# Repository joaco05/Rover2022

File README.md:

# Rover2022
Rover para clases iniciales. Cerrado y compacto para evitar desconexiones y problemas electricos. Basado en placa Controladora PCB BC2019 (Arduino Nano, driver motores, sensor ultrasonico, sensores IR, conectores) Alimentacion 2 x 3,7V (alimentacion del driver de motores, independiente de Arduino)<br><br>
<b>Printer 3D</b>
Se imprime sin soportes, altura 0,20 o 0,25. Solo las ruedas quedan mejor en modo VASE

<br><br>
<b>ARMADO</b>
El pack de baterias debe ubicarse lo mas adelante posible. Los soportes de motor deberan ir justo despues del borde curvo del chassis, de manera tal que el eje del motor quede al menos 10mm detras del borde.
Esto apunta a que el centro de gravedad se desplace mas cerca de los ejes permitiendo una mejor traccion y evitando patinada de ruedas.

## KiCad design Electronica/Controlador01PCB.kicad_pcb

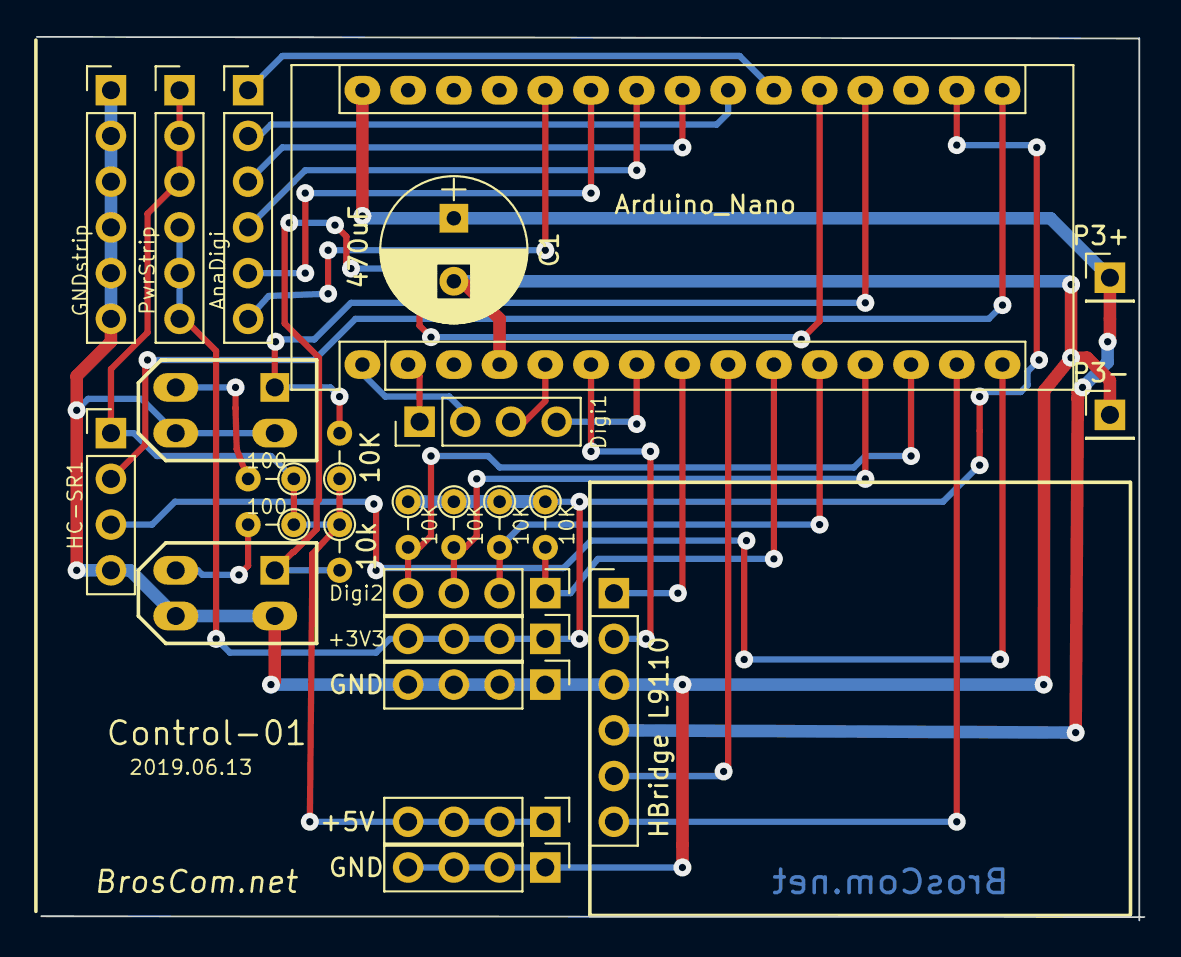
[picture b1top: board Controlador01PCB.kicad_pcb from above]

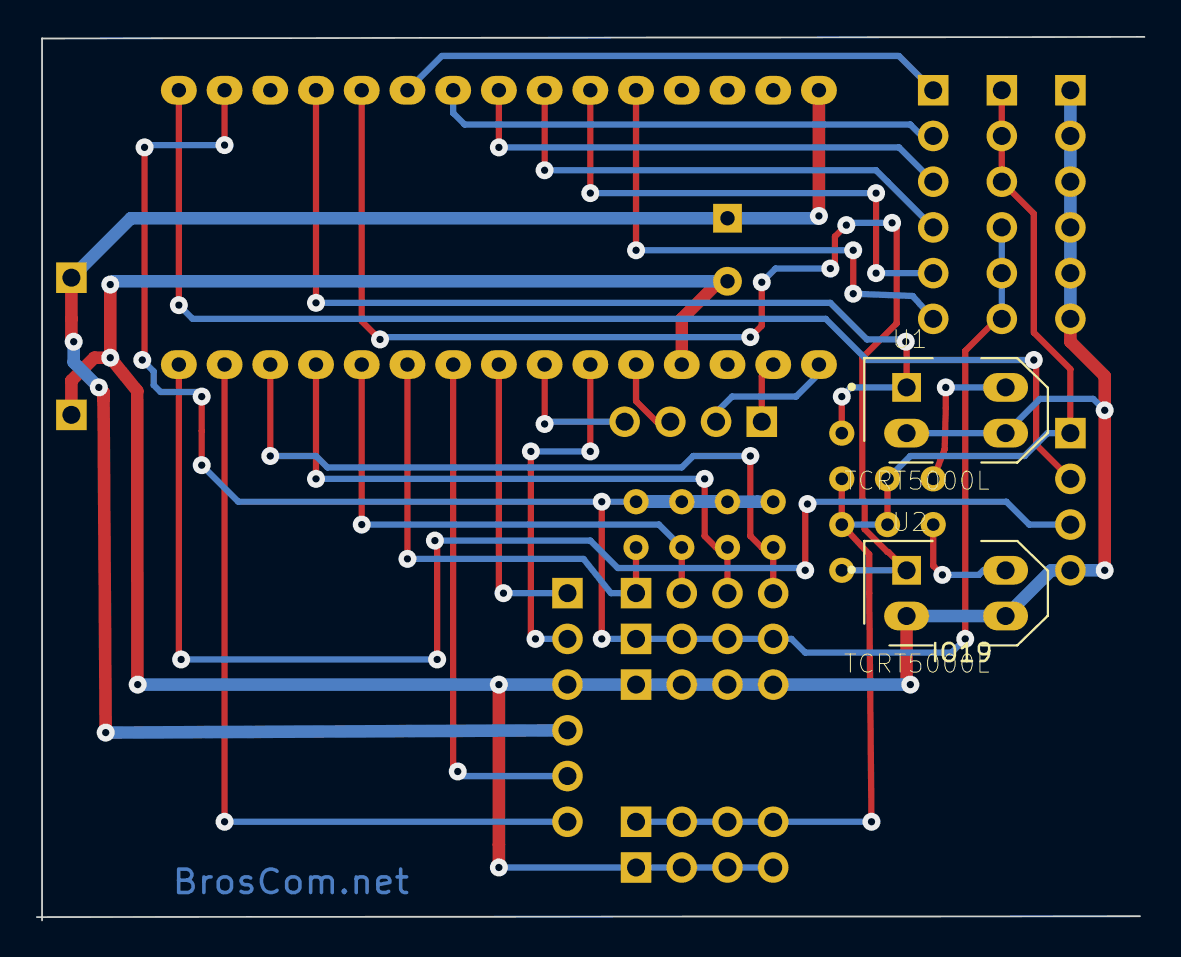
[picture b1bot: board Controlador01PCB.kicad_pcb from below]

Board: 2 copper layers, 61.5 x 49.1 mm, 25 parts (2 on the bottom side), 28 nets.

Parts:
A1: Arduino_Nano
C1: 470uF; CP_Radial_D8.0mm_P3.50mm
GNDstrip1: GNDstrip; Pin_Header_Straight_1x06_Pitch2.54mm
HC-SR1: Ultrasonic; Pin_Header_Straight_1x04_Pitch2.54mm
P1: HBridge L9110; Pin_Header_Straight_1x06_Pitch2.54mm
P2: AnaDigi; Pin_Header_Straight_1x06_Pitch2.54mm
P3: Digi1; Pin_Header_Straight_1x04_Pitch2.54mm
P3+, P3-: CONN_01X01; Pin_Header_Straight_1x01_Pitch2.54mm
P3G1, P4G1: GND; Pin_Header_Straight_1x04_Pitch2.54mm
P3V1: +5V; Pin_Header_Straight_1x04_Pitch2.54mm
P4: Digi2; Pin_Header_Straight_1x04_Pitch2.54mm
P4V1: +3V3; Pin_Header_Straight_1x04_Pitch2.54mm
PwrStrip1: PwrStrip; Pin_Header_Straight_1x06_Pitch2.54mm
R1, R5, R6, R7, R8: 10K; R_Axial_DIN0204_L3.6mm_D1.6mm_P2.54mm_Vertical
R2: 10k; R_Axial_DIN0204_L3.6mm_D1.6mm_P2.54mm_Vertical
R3, R4: 100; R_Axial_DIN0204_L3.6mm_D1.6mm_P2.54mm_Vertical
U1, U2: TCRT5000L; XDCR_TCRT5000L

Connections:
+3V3: A1.17, P4V1.1, P4V1.2, P4V1.3, P4V1.4, PwrStrip1.4, PwrStrip1.5, PwrStrip1.6, R5.1, R6.1, R7.1, R8.1
+5V: HC-SR1.1, P3V1.1, P3V1.2, P3V1.3, P3V1.4, PwrStrip1.1, PwrStrip1.2, PwrStrip1.3, R1.1, R2.1, R3.1, R4.1
D7: A1.10, P4.1, R5.2
D8: A1.11, P4.2, R6.2
D9: A1.12, P4.3, R7.2
D10: A1.13, P4.4, R8.2
GND: A1.4, C1.2, GNDstrip1.1, GNDstrip1.2, GNDstrip1.3, GNDstrip1.4, GNDstrip1.5, GNDstrip1.6, HC-SR1.4, P1.3, P3-.1, P3G1.1, P3G1.2, P3G1.3, P3G1.4, P4G1.1, P4G1.2, P4G1.3, P4G1.4, U1.2, U1.3, U2.2, U2.3
unnamed: A1.1, P3.2
unnamed: A1.2, P3.1
unnamed: A1.5, P3.3
unnamed: A1.6, P1.2
unnamed: A1.7, P3.4
unnamed: A1.8, P1.1
unnamed: A1.9, P1.5
unnamed: A1.14, P1.6
unnamed: A1.15, HC-SR1.3
unnamed: A1.16, HC-SR1.2
unnamed: A1.19, R1.2, U1.1
unnamed: A1.20, R2.2, U2.1
unnamed: A1.21, P2.1
unnamed: A1.22, P2.2
unnamed: A1.23, P2.3
unnamed: A1.24, P2.4
unnamed: A1.25, P2.5
unnamed: A1.26, P2.6
unnamed: R3.2, U1.4
unnamed: R4.2, U2.4
VCC: A1.30, C1.1, P1.4, P3+.1

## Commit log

2022-04-25 Create STL
2022-04-26 Create 1
2022-05-16 Create Joaco
